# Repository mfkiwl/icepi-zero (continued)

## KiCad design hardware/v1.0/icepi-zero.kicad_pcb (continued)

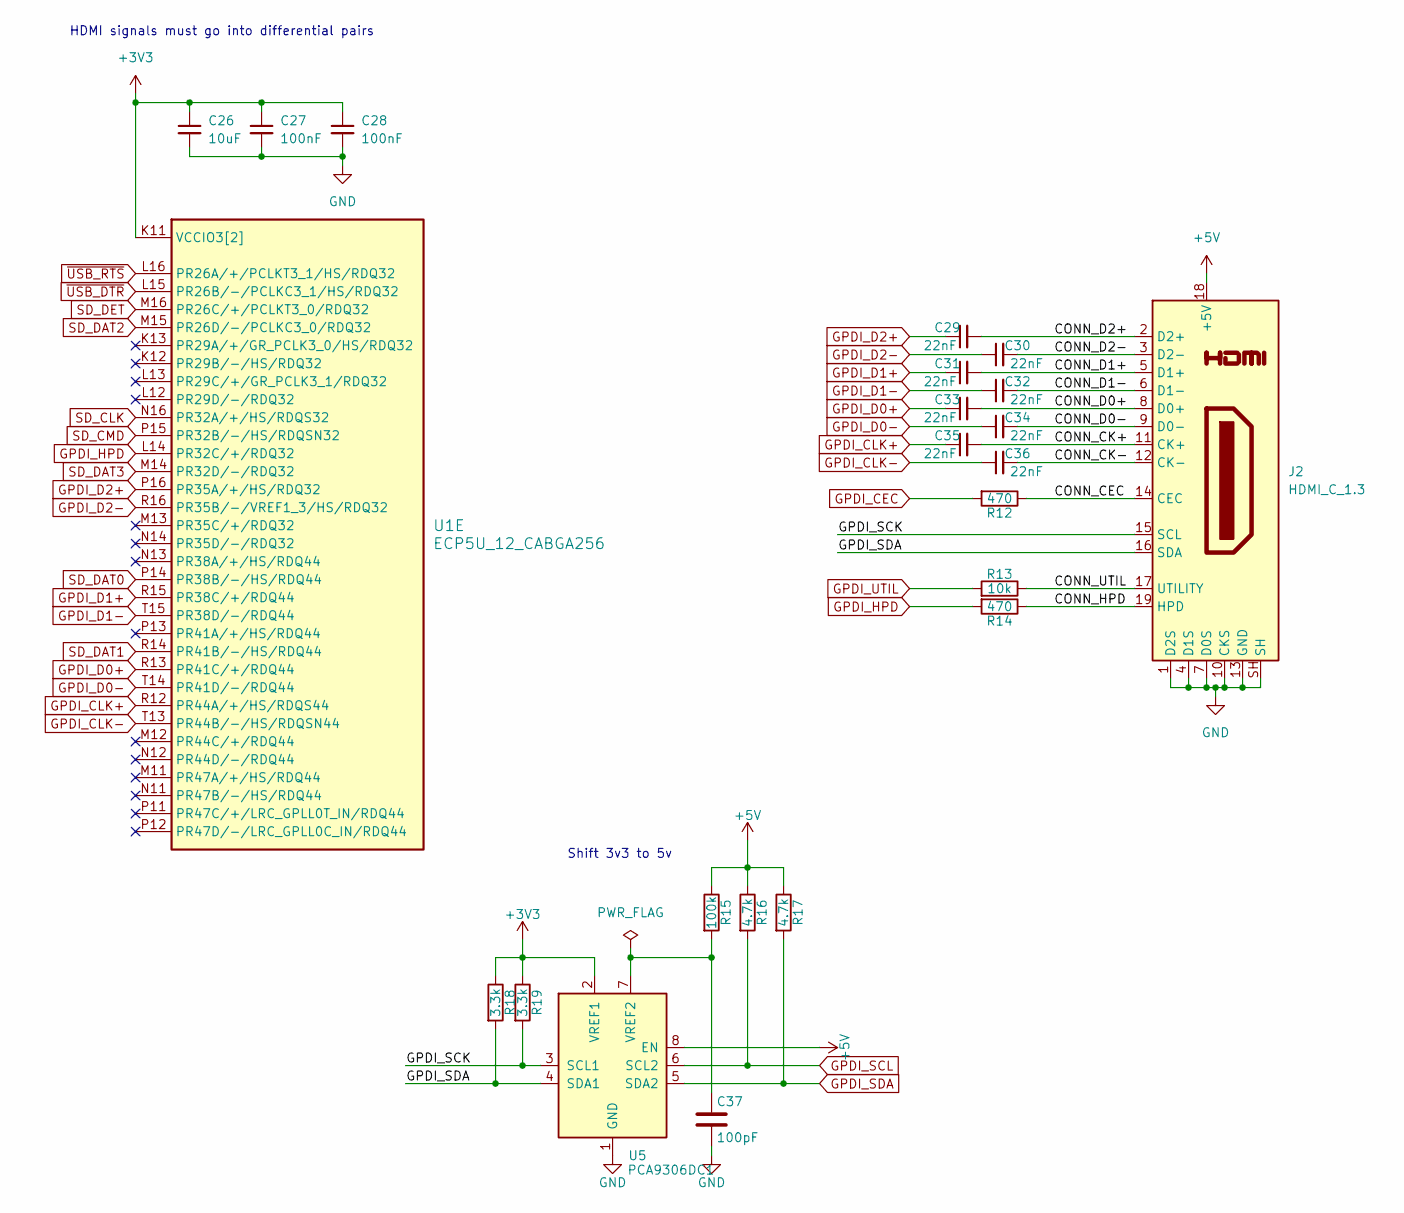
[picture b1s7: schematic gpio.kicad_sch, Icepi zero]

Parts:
C26: 10uF; C_0603_1608Metric; LCSC Part # C19702
C27, C28: 100nF; C_0402_1005Metric; LCSC Part # C307331
C29, C30, C31, C32, C33, C34, C35, C36: 22nF; C_0402_1005Metric; LCSC Part # C1532
C37: 100pF; C_0402_1005Metric; LCSC Part # C1546
J2: HDMI_C_1.3; XKB Connection A71-05H4-111N1; LCSC Part # C2682170
R12, R14: 470; R_0402_1005Metric; LCSC Part # C25117
R13: 10k; R_0402_1005Metric; LCSC Part # C25744
R15: 100k; R_0402_1005Metric; LCSC Part # C25741
R16, R17: 4.7k; R_0402_1005Metric; LCSC Part # C25900
R18, R19: 3.3k; R_0402_1005Metric; LCSC Part # C25890
U1: ECP5U_12_CABGA256; BGA-256_14.0x14.0mm_Layout16x16_P0.8mm_Ball0.45mm_Pad0.32mm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; LCSC Part # C1521614
U5: PCA9306DC1; VSSOP-8_2.3x2mm_P0.5mm; LCSC Part # C129510

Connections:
+3V3: C26.1, C27.1, C28.1, R18.1, R19.1, U1.K11 (VCCIO3[2]), U1.L11 (VCCIO3[2]), U5.2 (VREF1); also elsewhere on the board
+5V: J2.18 (+5V), R15.1, R16.1, R17.1, U5.8 (EN); also elsewhere on the board
/GPIO/CONN_CEC: J2.14 (CEC), R12.1
/GPIO/CONN_CK+: C35.2, J2.11 (CK+)
/GPIO/CONN_CK-: C36.2, J2.12 (CK-)
/GPIO/CONN_D0+: C33.2, J2.8 (D0+)
/GPIO/CONN_D0-: C34.2, J2.9 (D0-)
/GPIO/CONN_D1+: C31.2, J2.5 (D1+)
/GPIO/CONN_D1-: C32.2, J2.6 (D1-)
/GPIO/CONN_D2+: C29.2, J2.2 (D2+)
/GPIO/CONN_D2-: C30.2, J2.3 (D2-)
/GPIO/CONN_HPD: J2.19 (HPD), R14.1
/GPIO/CONN_UTIL: J2.17 (UTILITY), R13.1
/GPIO/GPDI_SCK: J2.15 (SCL), R19.2, U5.3 (SCL1)
GND: C26.2, C27.2, C28.2, C37.2, J2.1 (D2S), J2.4 (D1S), J2.7 (D0S), J2.10 (CKS), J2.13 (GND), J2.SH, U5.1 (GND); also elsewhere on the board
GPDI_CEC: R12.2; also elsewhere on the board
GPDI_CLK+: C35.1, U1.R12 (PR44A/+/HS/RDQS44)
GPDI_CLK-: C36.1, U1.T13 (PR44B/-/HS/RDQSN44)
GPDI_D0+: C33.1, U1.R13 (PR41C/+/RDQ44)
GPDI_D0-: C34.1, U1.T14 (PR41D/-/RDQ44)
GPDI_D1+: C31.1, U1.R15 (PR38C/+/RDQ44)
GPDI_D1-: C32.1, U1.T15 (PR38D/-/RDQ44)
GPDI_D2+: C29.1, U1.P16 (PR35A/+/HS/RDQ32)
GPDI_D2-: C30.1, U1.R16 (PR35B/-/VREF1_3/HS/RDQ32)
GPDI_HPD: R14.2, U1.L14 (PR32C/+/RDQ32)
GPDI_SCL: R16.2, U5.6 (SCL2); also elsewhere on the board
GPDI_SDA: J2.16 (SDA), R17.2, R18.2, U5.4 (SDA1), U5.5 (SDA2); also elsewhere on the board
GPDI_UTIL: R13.2; also elsewhere on the board
unnamed: C37.1, R15.2, U5.7 (VREF2)
SD_CLK: U1.N16 (PR32A/+/HS/RDQS32); also elsewhere on the board
SD_CMD: U1.P15 (PR32B/-/HS/RDQSN32); also elsewhere on the board
SD_DAT0: U1.P14 (PR38B/-/HS/RDQ44); also elsewhere on the board
SD_DAT1: U1.R14 (PR41B/-/HS/RDQ44); also elsewhere on the board
SD_DAT2: U1.M15 (PR26D/-/PCLKC3_0/RDQ32); also elsewhere on the board
SD_DAT3: U1.M14 (PR32D/-/RDQ32); also elsewhere on the board
SD_DET: U1.M16 (PR26C/+/PCLKT3_0/RDQ32); also elsewhere on the board
~USB_DTR: U1.L15 (PR26B/-/PCLKC3_1/HS/RDQ32); also elsewhere on the board
~USB_RTS: U1.L16 (PR26A/+/PCLKT3_1/HS/RDQ32); also elsewhere on the board

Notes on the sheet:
Shift 3v3 to 5v
HDMI signals must go into differential pairs

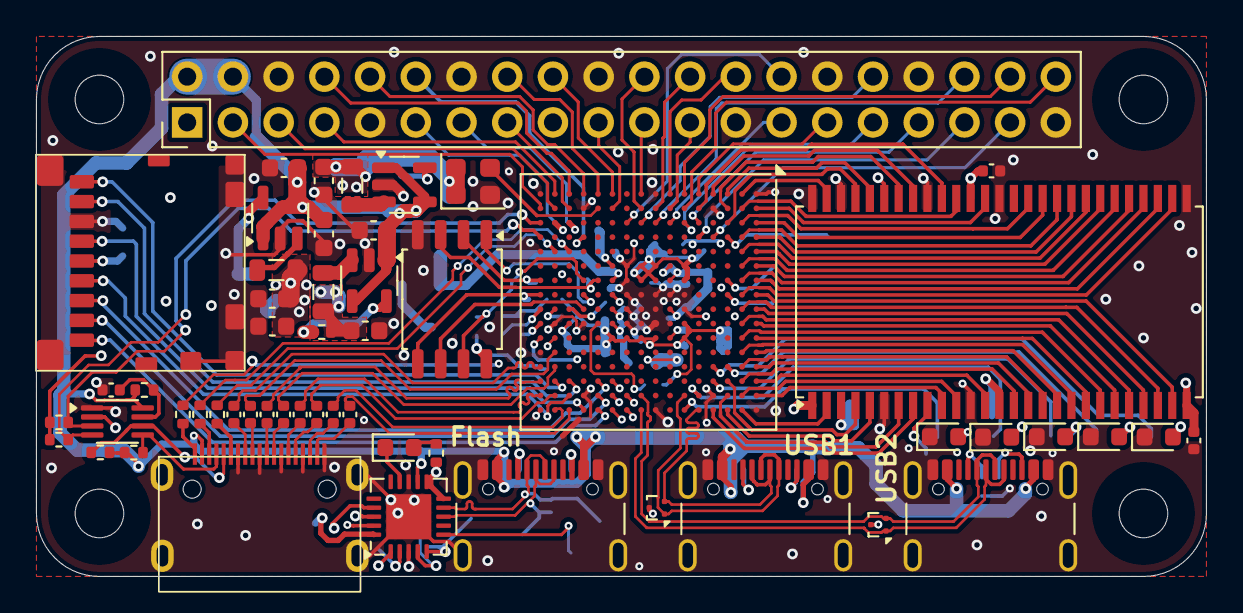
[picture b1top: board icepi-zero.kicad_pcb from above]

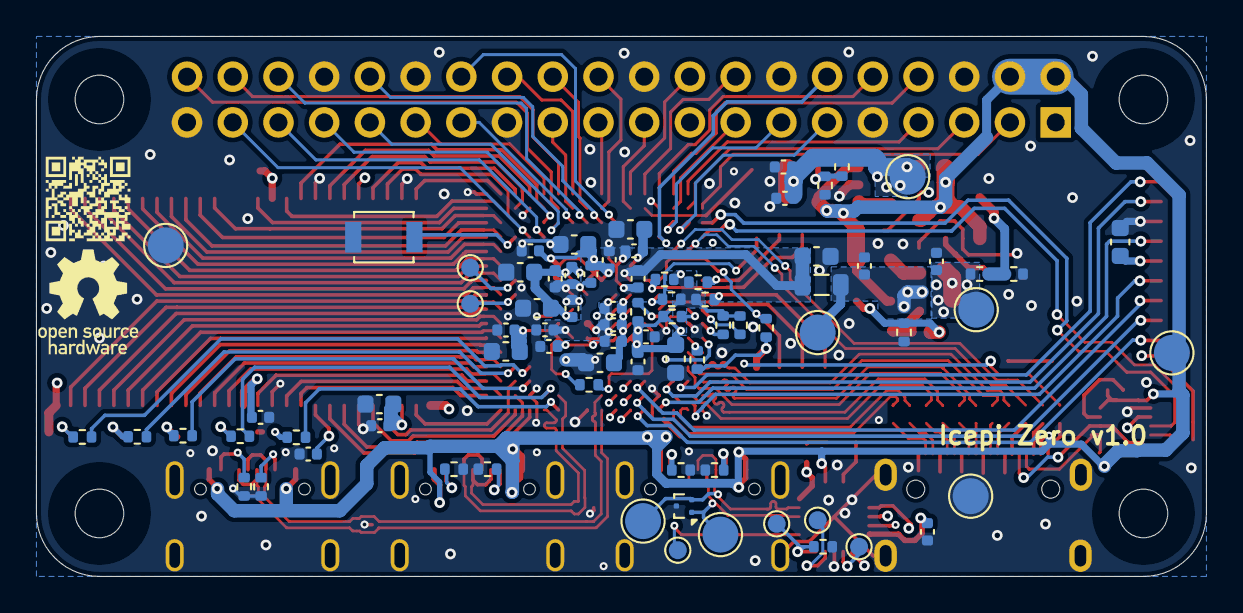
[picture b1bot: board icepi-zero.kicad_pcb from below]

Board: 4 copper layers, 65.0 x 30.0 mm, 137 parts (79 on the bottom side), 158 nets.

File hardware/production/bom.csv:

Designator,Footprint,Quantity,Value,LCSC Part #
"C1, C19, C23, C26, C42, C45, C47, C49, C7, C8, C9",0603,11,10uF,C19702
"C10, C11, C12, C13, C14, C15, C18, C2, C20, C21, C24, C25, C27, C28, C38, C39, C40, C41, C43, C44, C46, C48, C50, C51, C52, C6",0402,26,100nF,C307331 
"C16, C17, C22, C3, C4, C5",0603,6,22uF,C59461 
"C29, C30, C31, C32, C33, C34, C35, C36",0402,8,22nF,C1532
C37,0402,1,100pF,C1546 
"D1, D2, D3, D4, D5",0603,5,WHITE,C2290
D6,0603,1,RED,C2286 
FB1,0805,1,100R@100MHz,C1015
J2,XKB Connection A71-05H4-111N1,1,HDMI_C_1.3,C2682170
"J3, J4, J5",USB_C_Receptacle_GCT_USB4105-xx-A_16P_TopMnt_Horizontal,3,USB_C_Receptacle_USB2.0_14P,C2765186
J6,microSD_HC_SOFNG_TF-008,1,Micro_SD_Card_Det2,C428465
"L1, L2, L3",0805,3,2.2uH,C1043
"R1, R12, R14, R2, R3, R4, R5",0402,7,470,C25117
"R10, R36, R37, R38, R8",0402,5,15k,C25756 
"R11, R18, R19",0402,3,3.3k,C25890 
"R13, R32, R33, R34, R35, R6",0402,6,10k,C25744
R15,0402,1,100k,C25741
"R16, R17, R22, R23, R24, R25, R31, R9",0402,8,4.7k,C25900 
"R20, R21, R26, R27, R29, R30",0402,6,5.1k,C25905 
R28,0402,1,100,C25076 
R7,0402,1,12k,C25752
SW1,SW_SPST_TL3342,1,SW_Push,C318884
"TP10, TP11, TP12, TP9",TestPoint_Pad_D1.0mm,4,TestPoint,
U1,BGA-256_14.0x14.0mm_Layout16x16_P0.8mm_Ball0.45mm_Pad0.32mm_NSMD,1,ECP5U_12_CABGA256,C1521614
U10,TSOP-II-54_22.2x10.16mm_P0.8mm,1,W9825G6KH,C62246
U11,SOIC-8_5.3x5.3mm_P1.27mm,1,W25Q128JVS,C97521
"U2, U3, U4",SOT-23-5,3,TLV62569DBV,C141836
U5,VSSOP-8_2.3x2mm_P0.5mm,1,PCA9306DC1,C129510
U6,QFN-20-1EP_4x4mm_P0.5mm_EP2.5x2.5mm,1,FT231XQ,C132159
"U7, U8, U9",Texas_DRT-3,3,TPD2EUSB30A,C3011197
Y1,Oscillator_SMD_SiT_PQFN-4Pin_2.5x2.0mm,1,SITxxxxxx-1x-33E-50.000000,C1182928

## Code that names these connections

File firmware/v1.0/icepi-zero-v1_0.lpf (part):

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LOCATE COMP "sd_dat[3]" SITE "M14";
IOBUF  PORT "sd_dat[3]" IO_TYPE=LVCMOS33 PULLMODE=UP DRIVE=4;
LOCATE COMP "sd_clk" SITE "N16";
IOBUF  PORT "sd_clk" IO_TYPE=LVCMOS33 PULLMODE=UP DRIVE=4;
LOCATE COMP "sd_cmd" SITE "P15";
IOBUF  PORT "sd_cmd" IO_TYPE=LVCMOS33 PULLMODE=UP DRIVE=4;
LOCATE COMP "sd_det" SITE "M16";
IOBUF  PORT "sd_det" IO_TYPE=LVCMOS33 PULLMODE=UP DRIVE=4;

# USB
LOCATE COMP "usb_dp[0]" SITE "F15";
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
# SPI Flash
LOCATE COMP "flash_cs" SITE "N8";
IOBUF  PORT "flash_cs" IO_TYPE=LVCMOS33 PULLMODE=UP DRIVE=4;
LOCATE COMP "flash_clk" SITE "N9";
IOBUF  PORT "flash_clk" IO_TYPE=LVCMOS33 PULLMODE=UP DRIVE=4;
LOCATE COMP "flash_mosi" SITE "T8";
IOBUF  PORT "flash_mosi" IO_TYPE=LVCMOS33 PULLMODE=UP DRIVE=4;
LOCATE COMP "flash_miso" SITE "T7";
IOBUF  PORT "flash_miso" IO_TYPE=LVCMOS33 PULLMODE=UP DRIVE=4;
LOCATE COMP "flash_wp" SITE "M7";
IOBUF  PORT "flash_wp" IO_TYPE=LVCMOS33 PULLMODE=UP DRIVE=4;
LOCATE COMP "flash_reset" SITE "N7";
IOBUF  PORT "flash_reset" IO_TYPE=LVCMOS33 PULLMODE=UP DRIVE=4;

# Testpoints
LOCATE COMP "tp1" SITE "C7";
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
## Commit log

2025-04-26 Init
2025-04-29 Start of everything
2025-05-01 Routed most of sdram
2025-05-03 Routed power
2025-05-03 Added the decoupling capacitors
2025-05-04 V1.0 Final Revision and Readme documentation
2025-05-04 Fix grammar
2025-05-04 Add pictures
2025-05-04 Fix level shifter EN voltage error
2025-05-06 Add a revision
2025-05-08 Pre-prod fixes
2025-05-08 Add a button
2025-05-10 Final revision
2025-05-12 Last checks
2025-05-13 Final production files
2025-05-19 Stash v1.0, start of firmware
2025-05-21 Forgot to commit yesterday
2025-05-21 Finish lpf
2025-05-22 Add blinky example
2025-05-23 Counter example start - button on off
2025-05-24 Counter
2025-05-25 Make build system
2025-05-25 Add better gitignore
2025-05-25 Add docs
2025-05-26 UART demo
2025-05-27 Patch readme
2025-05-28 It's minigpdi, not micro!
2025-05-28 Add memtest
2025-05-29 Improve build script
2025-08-25 DVI multires
